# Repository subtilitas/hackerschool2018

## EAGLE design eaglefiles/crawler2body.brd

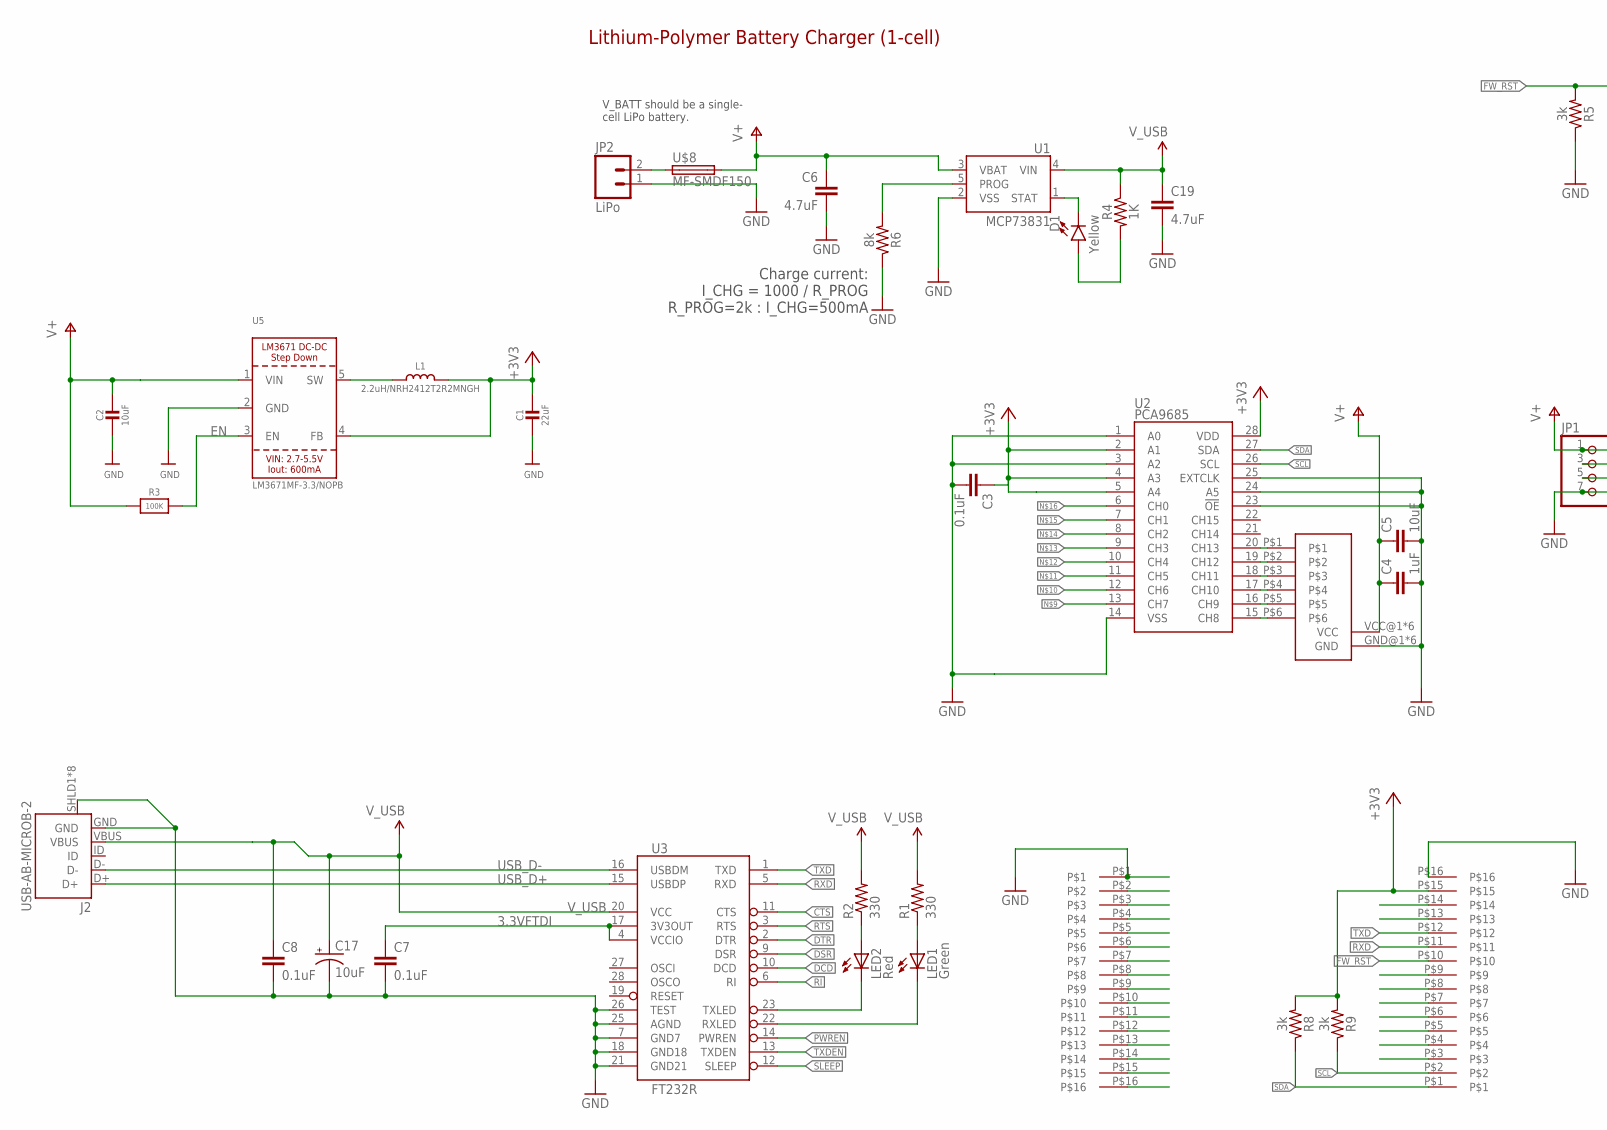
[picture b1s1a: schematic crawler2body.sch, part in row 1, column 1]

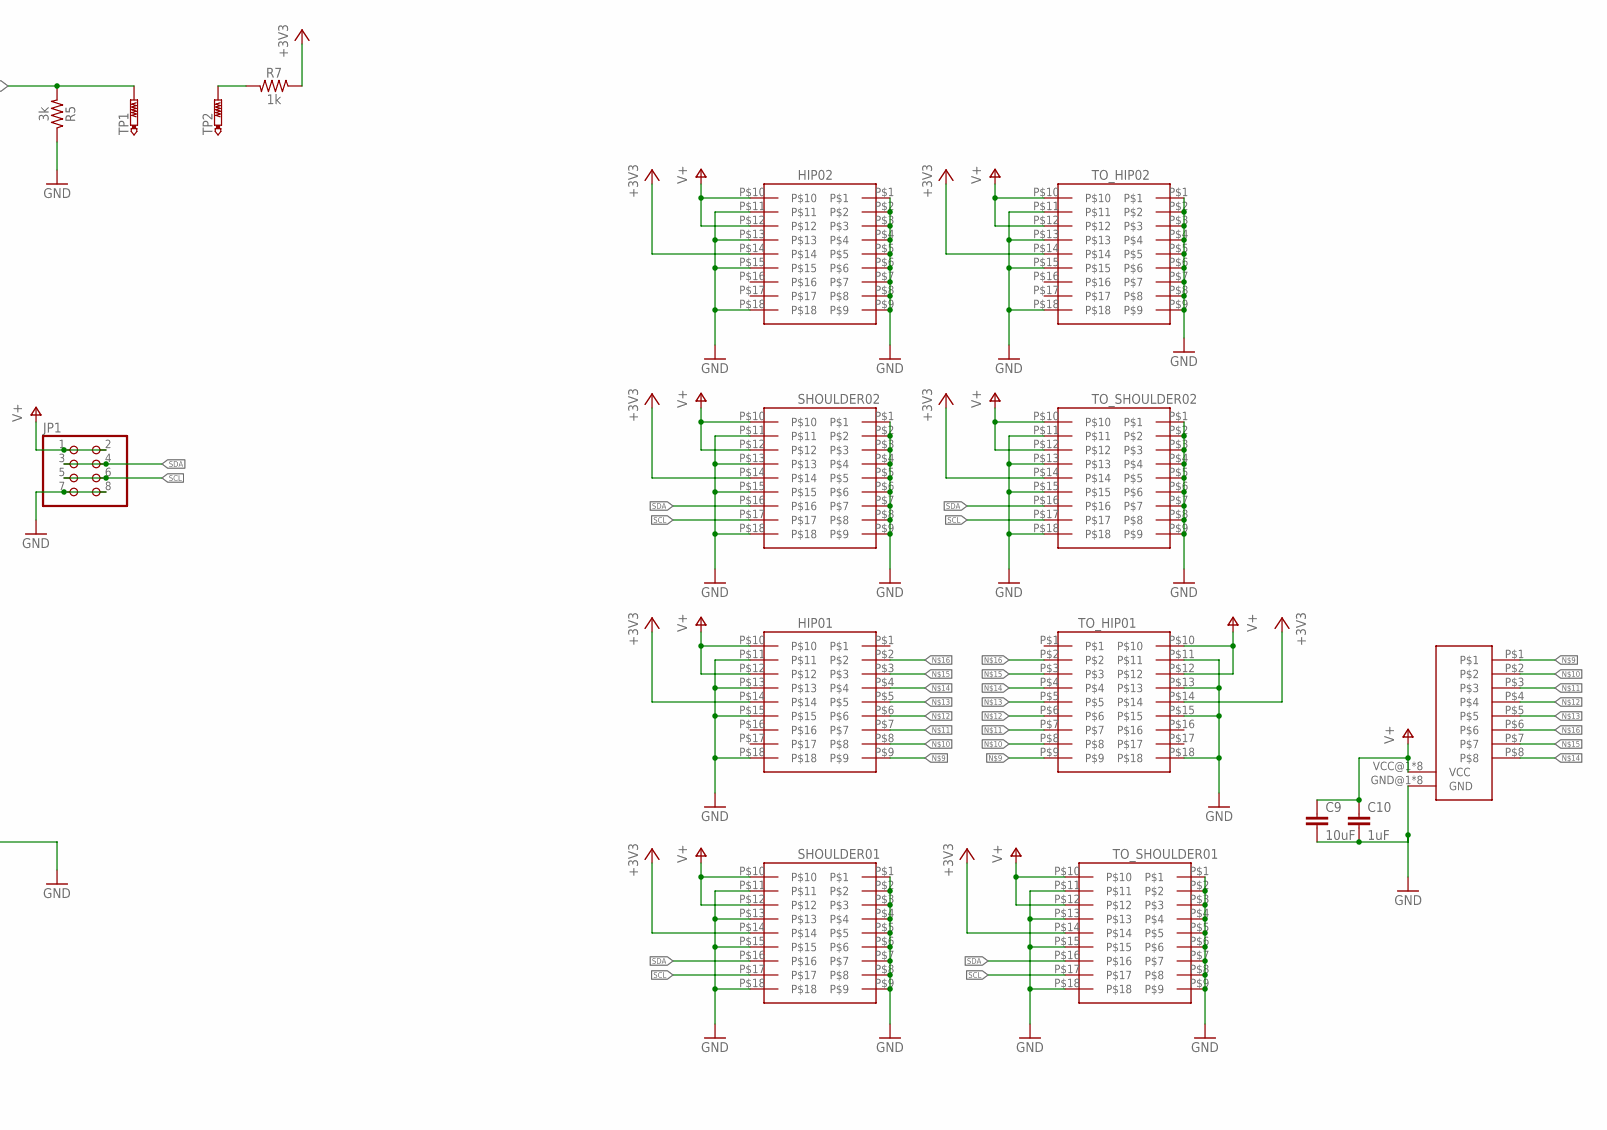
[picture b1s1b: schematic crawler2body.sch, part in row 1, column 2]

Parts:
C1: 22uF; 0805-NO
C2: 10uF; 0805-NO
C3, C7, C8: 0.1uF; 0603-CAP
C4, C10: 1uF; C1210
C5, C9: 10uF; C1210
C6, C19: 4.7uF; 0603
C17: 10uF; EIA3216
D1: Yellow; LED-0603
HIP01, HIP02: BOARD2BOARD_SLOT
J2: USB-AB-MICROB-2; USB-MICROB-10118194
JP1: PINHD-2X4; 2X04
JP2: LiPo; JST-2-PTH-NS
L1: 2.2uH/NRH2412T2R2MNGH; INDUCTOR_TAIYOYUDEN_NRH2412T
LED1: Green; LED-0603@1
LED2: Red; LED-0603@1
R1, R2: 330; 0603-RES
R3: 100K; 0805-NO
R4: 1K; 0603
R5, R8, R9: 3k; 0603
R6: 8k; 0603
R7: 1k; 0603
SHOULDER01, SHOULDER02: BOARD2BOARD_SLOT
TO_HIP01, TO_HIP02: BOARD2BOARD
TO_SHOULDER01, TO_SHOULDER02: BOARD2BOARD
TP1, TP2: PTR1TP15SQ; TP15SQ
U1: MCP73831; SOT23-5
U2: PCA9685; TSSOP-28_4MM
U3: FT232R; SSOP28DB
U5: LM3671MF-3.3/NOPB; SOT23-5
U$1, U$2: SPLITPAC_OMEGA2; SPLITTED_OMEGA2
U$3: RC8CHAN
U$4: RC6CHAN
U$8: MF-SMDF150; MF-SMDF050

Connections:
3.3VFTDI: C7.1, U3.4 (VCCIO), U3.17 (3V3OUT)
+3V3: C1.1, C3.1, HIP01.P$14, HIP02.P$14, L1.2, R7.1, R8.2, R9.2, SHOULDER01.P$14, SHOULDER02.P$14, TO_HIP01.P$14, TO_HIP02.P$14, TO_SHOULDER01.P$14, TO_SHOULDER02.P$14, U2.2 (A1), U2.4 (A3), U2.5 (A4), U2.28 (VDD), U5.4 (FB), U$2.P$15
CTS: U3.11 (CTS)
DCD: U3.10 (DCD)
DSR: U3.9 (DSR)
DTR: U3.2 (DTR)
EN: R3.2, U5.3 (EN)
FW_RST: R5.2, TP1.TP, U$2.P$10
GND: C1.2, C2.2, C3.2, C4.2, C5.2, C6.2, C7.2, C8.2, C9.2, C10.2, C17.C (-), C19.2, HIP01.P$11, HIP01.P$13, HIP01.P$15, HIP01.P$18, HIP02.P$1, HIP02.P$2, HIP02.P$3, HIP02.P$4, HIP02.P$5, HIP02.P$6, HIP02.P$7, HIP02.P$8, HIP02.P$9, HIP02.P$11, HIP02.P$13, HIP02.P$15, HIP02.P$18, J2.GND, J2.SHLD1 (SHIELD), J2.SHLD2 (SHIELD), J2.SHLD3 (SHIELD), J2.SHLD4 (SHIELD), J2.SHLD5 (SHIELD), J2.SHLD6 (SHIELD), J2.SHLD7 (SHIELD), J2.SHLD8 (SHIELD), JP1.7, JP1.8, JP2.1, R5.1, R6.1, SHOULDER01.P$1, SHOULDER01.P$2, SHOULDER01.P$3, SHOULDER01.P$4, SHOULDER01.P$5, SHOULDER01.P$6, SHOULDER01.P$7, SHOULDER01.P$8, SHOULDER01.P$9, SHOULDER01.P$11, SHOULDER01.P$13, SHOULDER01.P$15, SHOULDER01.P$18, SHOULDER02.P$1, SHOULDER02.P$2, SHOULDER02.P$3, SHOULDER02.P$4, SHOULDER02.P$5, SHOULDER02.P$6, SHOULDER02.P$7, SHOULDER02.P$8, SHOULDER02.P$9, SHOULDER02.P$11, SHOULDER02.P$13, SHOULDER02.P$15, SHOULDER02.P$18, TO_HIP01.P$11, TO_HIP01.P$13, TO_HIP01.P$15, TO_HIP01.P$18, TO_HIP02.P$1, TO_HIP02.P$2, TO_HIP02.P$3, TO_HIP02.P$4, TO_HIP02.P$5, TO_HIP02.P$6, TO_HIP02.P$7, TO_HIP02.P$8, TO_HIP02.P$9, TO_HIP02.P$11, TO_HIP02.P$13, TO_HIP02.P$15, TO_HIP02.P$18, TO_SHOULDER01.P$1, TO_SHOULDER01.P$2, TO_SHOULDER01.P$3, TO_SHOULDER01.P$4, TO_SHOULDER01.P$5, TO_SHOULDER01.P$6, TO_SHOULDER01.P$7, TO_SHOULDER01.P$8, TO_SHOULDER01.P$9, TO_SHOULDER01.P$11, TO_SHOULDER01.P$13, TO_SHOULDER01.P$15, TO_SHOULDER01.P$18, TO_SHOULDER02.P$1, TO_SHOULDER02.P$2, TO_SHOULDER02.P$3, TO_SHOULDER02.P$4, TO_SHOULDER02.P$5, TO_SHOULDER02.P$6, TO_SHOULDER02.P$7, TO_SHOULDER02.P$8, TO_SHOULDER02.P$9, TO_SHOULDER02.P$11, TO_SHOULDER02.P$13, TO_SHOULDER02.P$15, TO_SHOULDER02.P$18, U1.2 (VSS), U2.1 (A0), U2.3 (A2), U2.14 (VSS), U2.23 (!OE), U2.24 (A5), U2.25 (EXTCLK), U3.7 (GND7), U3.18 (GND18), U3.21 (GND21), U3.25 (AGND), U3.26 (TEST), U5.2 (GND), U$1.P$1, U$2.P$16, U$3.GND@1 (GND), U$3.GND@2 (GND), U$3.GND@3 (GND), U$3.GND@4 (GND), U$3.GND@5 (GND), U$3.GND@6 (GND), U$3.GND@7 (GND), U$3.GND@8 (GND), U$4.GND@1 (GND), U$4.GND@2 (GND), U$4.GND@3 (GND), U$4.GND@4 (GND), U$4.GND@5 (GND), U$4.GND@6 (GND)
unnamed: L1.1, U5.5 (SW)
unnamed: D1.A, R4.2
unnamed: U2.20 (CH13), U$4.P$1
unnamed: U2.19 (CH12), U$4.P$2
unnamed: U2.18 (CH11), U$4.P$3
unnamed: U2.17 (CH10), U$4.P$4
unnamed: U2.16 (CH9), U$4.P$5
unnamed: U2.15 (CH8), U$4.P$6
unnamed: HIP01.P$9, TO_HIP01.P$9, U2.13 (CH7), U$3.P$1
unnamed: HIP01.P$8, TO_HIP01.P$8, U2.12 (CH6), U$3.P$2
unnamed: HIP01.P$7, TO_HIP01.P$7, U2.11 (CH5), U$3.P$3
unnamed: HIP01.P$6, TO_HIP01.P$6, U2.10 (CH4), U$3.P$4
unnamed: HIP01.P$5, TO_HIP01.P$5, U2.9 (CH3), U$3.P$5
unnamed: HIP01.P$4, TO_HIP01.P$4, U2.8 (CH2), U$3.P$8
unnamed: HIP01.P$3, TO_HIP01.P$3, U2.7 (CH1), U$3.P$7
unnamed: HIP01.P$2, TO_HIP01.P$2, U2.6 (CH0), U$3.P$6
unnamed: LED2.A, R2.1
unnamed: LED1.A, R1.1
unnamed: D1.C, U1.1 (STAT)
unnamed: R7.2, TP2.TP
unnamed: R6.2, U1.5 (PROG)
unnamed: JP2.2, U$8.1
PWREN: U3.14 (PWREN)
RI: U3.6 (RI)
RTS: U3.3 (RTS)
RXD: U3.5 (RXD), U$2.P$11
RXLED: LED1.C, U3.22 (RXLED)
SCL: JP1.5, JP1.6, R9.1, SHOULDER01.P$17, SHOULDER02.P$17, TO_SHOULDER01.P$17, TO_SHOULDER02.P$17, U2.26 (SCL), U$2.P$2
SDA: JP1.3, JP1.4, R8.1, SHOULDER01.P$16, SHOULDER02.P$16, TO_SHOULDER01.P$16, TO_SHOULDER02.P$16, U2.27 (SDA), U$2.P$1
SLEEP: U3.12 (SLEEP)
TXD: U3.1 (TXD), U$2.P$12
TXDEN: U3.13 (TXDEN)
TXLED: LED2.C, U3.23 (TXLED)
USB_D+: J2.D+, U3.15 (USBDP)
USB_D-: J2.D-, U3.16 (USBDM)
V+: C2.1, C4.1, C5.1, C6.1, C9.1, C10.1, HIP01.P$10, HIP01.P$12, HIP02.P$10, HIP02.P$12, JP1.1, JP1.2, R3.1, SHOULDER01.P$10, SHOULDER01.P$12, SHOULDER02.P$10, SHOULDER02.P$12, TO_HIP01.P$10, TO_HIP01.P$12, TO_HIP02.P$10, TO_HIP02.P$12, TO_SHOULDER01.P$10, TO_SHOULDER01.P$12, TO_SHOULDER02.P$10, TO_SHOULDER02.P$12, U1.3 (VBAT), U5.1 (VIN), U$3.VCC@1 (VCC), U$3.VCC@2 (VCC), U$3.VCC@3 (VCC), U$3.VCC@4 (VCC), U$3.VCC@5 (VCC), U$3.VCC@6 (VCC), U$3.VCC@7 (VCC), U$3.VCC@8 (VCC), U$4.VCC@1 (VCC), U$4.VCC@2 (VCC), U$4.VCC@3 (VCC), U$4.VCC@4 (VCC), U$4.VCC@5 (VCC), U$4.VCC@6 (VCC), U$8.2
V_USB: C8.1, C17.A (+), C19.1, J2.VBUS, R1.2, R2.2, R4.1, U1.4 (VIN), U3.20 (VCC)

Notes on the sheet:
V_BATT should be a single- cell LiPo battery.
Charge current: I_CHG = 1000 / R_PROG R_PROG=2k : I_CHG=500mA
Lithium-Polymer Battery Charger (1-cell)

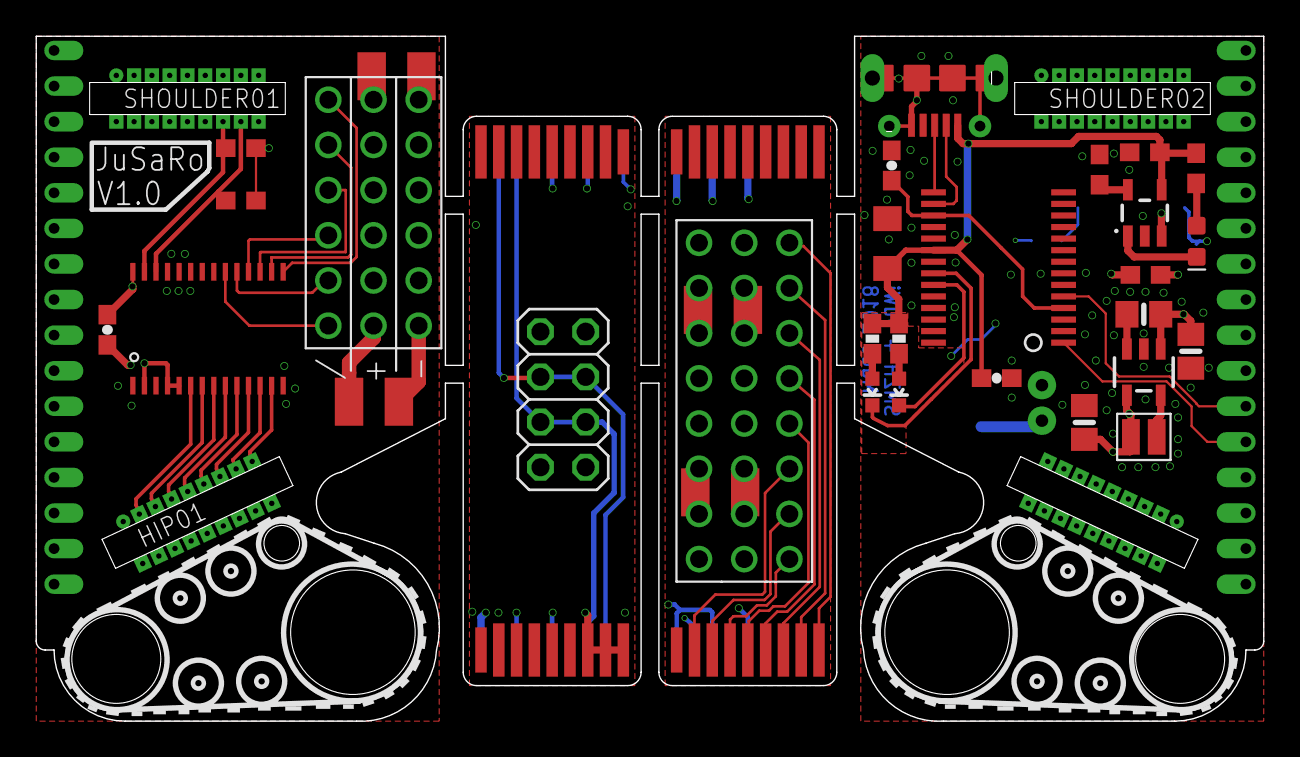
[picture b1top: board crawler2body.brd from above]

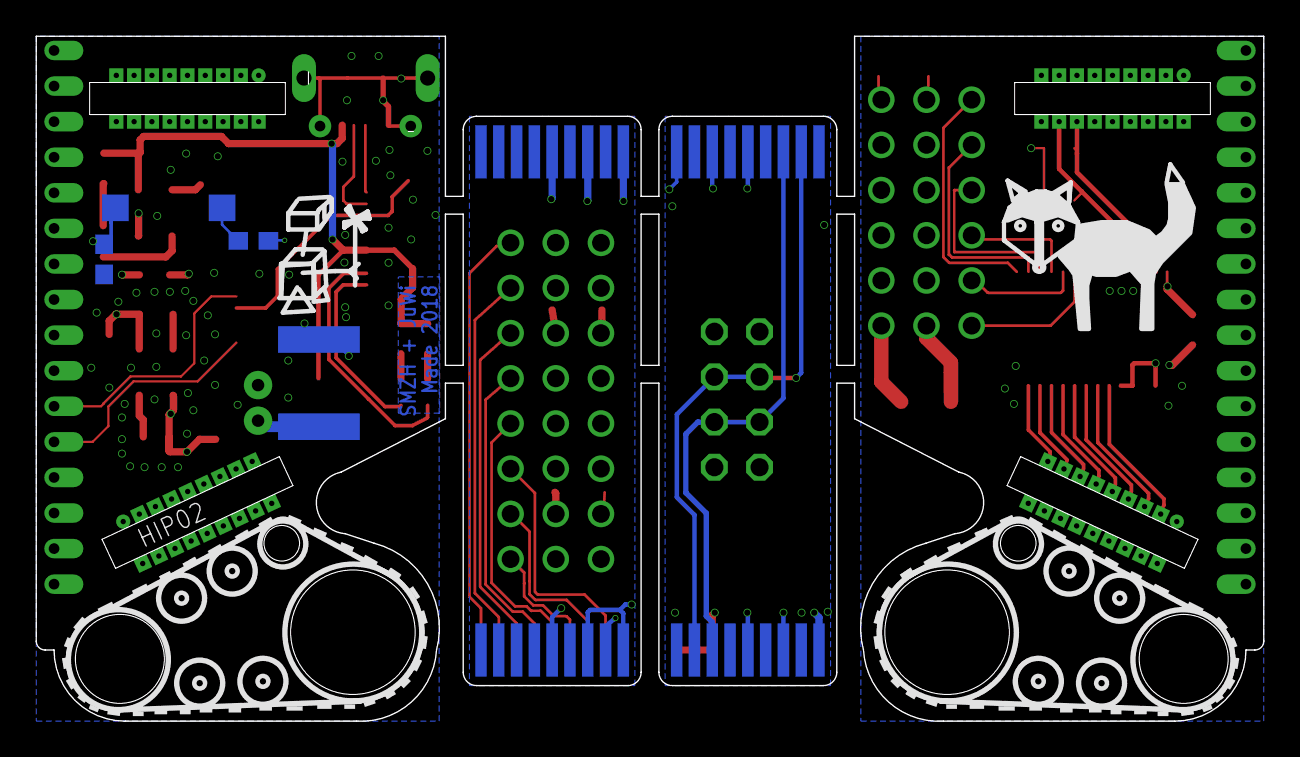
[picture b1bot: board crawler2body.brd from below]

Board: 4 copper layers, 69.0 x 38.5 mm, 47 parts (7 on the bottom side), 37 nets.

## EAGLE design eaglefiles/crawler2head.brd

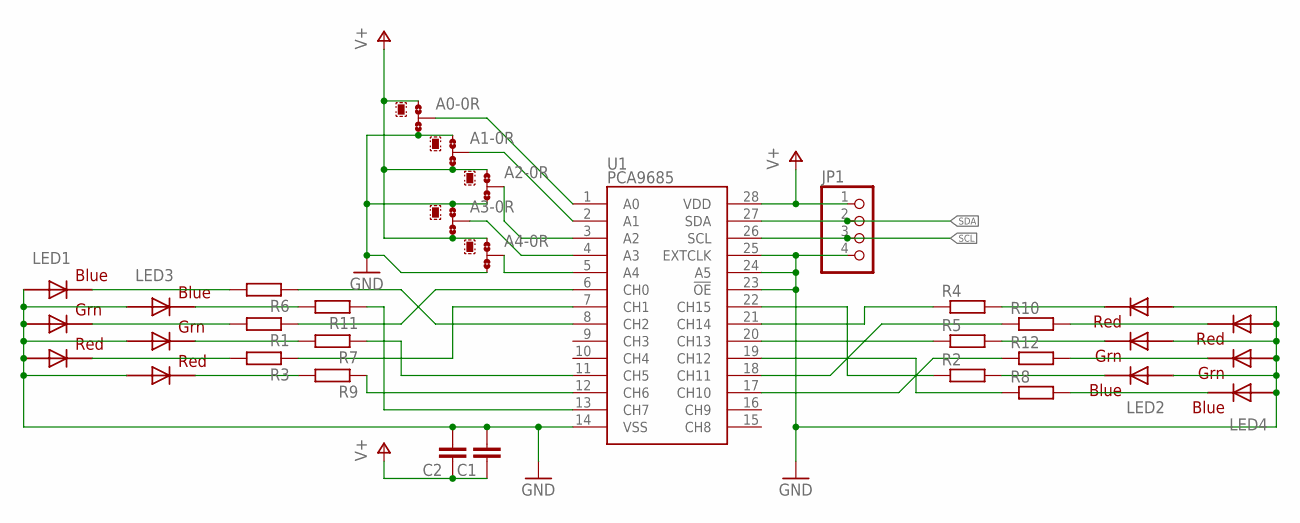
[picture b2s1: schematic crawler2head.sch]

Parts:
A0: A0; B0R-JMP
A1, A2, A3, A4: 0R-JUMPB; B0R-JMP
C1: C-EUC3216; C3216
C2: C-EUC0603; C0603
JP1: PINHD-1X4/90; 1X04/90
LED1, LED2, LED3, LED4: RGBLED5050
R1, R2, R3, R4, R5, R6, R7, R8, R9, R10, R11, R12: R-EU_R0603; R0603
U1: PCA9685; TSSOP-28_4MM

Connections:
GND: A0.3, A1.1, A2.3, A3.1, A4.3, C1.2, C2.2, JP1.4, LED1.1 (GREEN_A), LED1.2 (RED_A), LED1.3 (BLUE_A), LED2.1 (GREEN_A), LED2.2 (RED_A), LED2.3 (BLUE_A), LED3.1 (GREEN_A), LED3.2 (RED_A), LED3.3 (BLUE_A), LED4.1 (GREEN_A), LED4.2 (RED_A), LED4.3 (BLUE_A), U1.14 (VSS), U1.23 (!OE), U1.24 (A5), U1.25 (EXTCLK)
unnamed: A4.2, U1.5 (A4)
unnamed: A3.2, U1.4 (A3)
unnamed: A2.2, U1.3 (A2)
unnamed: A1.2, U1.2 (A1)
unnamed: A0.2, U1.1 (A0)
unnamed: LED2.5 (RED_C), R4.2
unnamed: LED2.6 (GREEN_C), R5.2
unnamed: LED2.4 (BLUE_C), R2.2
unnamed: LED4.5 (RED_C), R10.2
unnamed: LED4.6 (GREEN_C), R12.2
unnamed: LED4.4 (BLUE_C), R8.2
unnamed: R2.1, U1.22 (CH15)
unnamed: R4.1, U1.21 (CH14)
unnamed: R5.1, U1.20 (CH13)
unnamed: R8.1, U1.19 (CH12)
unnamed: R10.1, U1.18 (CH11)
unnamed: R12.1, U1.17 (CH10)
unnamed: R11.1, U1.13 (CH7)
unnamed: R9.1, U1.12 (CH6)
unnamed: R7.1, U1.11 (CH5)
unnamed: LED3.5 (RED_C), R9.2
unnamed: LED3.6 (GREEN_C), R7.2
unnamed: LED3.4 (BLUE_C), R11.2
unnamed: LED1.5 (RED_C), R3.2
unnamed: LED1.6 (GREEN_C), R1.2
unnamed: LED1.4 (BLUE_C), R6.2
unnamed: R6.1, U1.8 (CH2)
unnamed: R3.1, U1.7 (CH1)
unnamed: R1.1, U1.6 (CH0)
SCL: JP1.3, U1.26 (SCL)
SDA: JP1.2, U1.27 (SDA)
V+: A0.1, A1.3, A2.1, A3.3, A4.1, C1.1, C2.1, JP1.1, U1.28 (VDD)

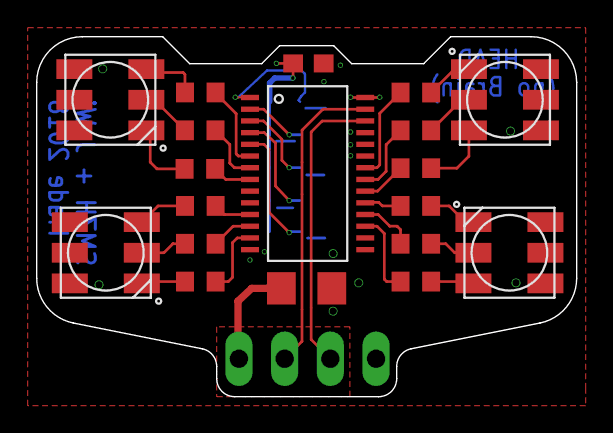
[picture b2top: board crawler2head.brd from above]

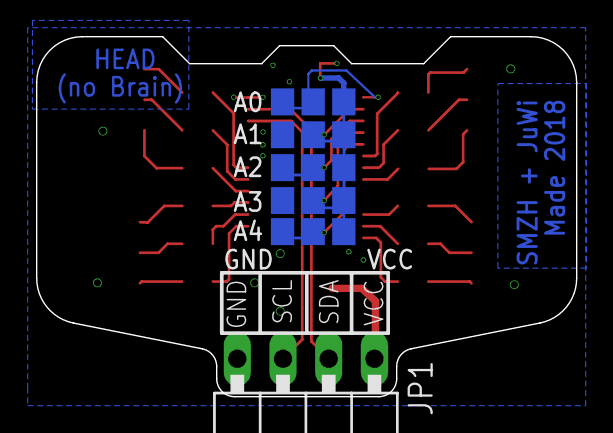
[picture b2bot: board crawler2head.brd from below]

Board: 4 copper layers, 30.0 x 20.0 mm, 25 parts (6 on the bottom side), 33 nets.

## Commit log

2018-01-31 initial
2018-02-01 review
2018-02-01 added stl of flattened pcb
2018-02-02 Review: crawler2body
2018-02-05 review 2
2018-02-06 Review-review-review Signed-off-by: Julian <julian.wingert@subtilitas.de>
2018-02-07 REVIEW2010230495094059 Signed-off-by: Julian <julian.wingert@subtilitas.de>
2018-02-07 Added drawings
2018-02-07 reviewed & tagged Signed-off-by: Julian <julian.wingert@subtilitas.de>
2018-02-09 ORDERED VERSION!!!!11elf Signed-off-by: Julian <julian.wingert@subtilitas.de>
2018-02-16 fixed wrong chematic for head
2018-02-22 fixed min distance
2018-04-30 unknown state

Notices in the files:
parts and their libraries:
SparkFun-IC-Special-Function: Licensing: Creative Commons ShareAlike 4.0 International - https://creativecommons.org/licenses/by-sa/4.0
SparkFun-Capacitors: Licensing: CC v3.0 Share-Alike You are welcome to use this library for commercial purposes.
